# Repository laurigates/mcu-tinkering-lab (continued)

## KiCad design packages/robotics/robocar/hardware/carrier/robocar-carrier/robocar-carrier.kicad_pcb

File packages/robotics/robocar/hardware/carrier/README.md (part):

# robocar carrier PCB

> **Before paying for an order**, Lauri does the bench checks in
> [Pre-order checks still owed](#pre-order-checks-still-owed-lauri);
> [`board.toml`](board.toml) marks every unmeasured dimension (#750).

The **main board**: one 100 × 100 mm, 2-layer PCB, screwed to the chassis (no
ready-made plate; the chassis is drilled to match H1–H4), that replaces the
hand-wired harness in [`WIRING.md`](../../WIRING.md). It carries the motor
driver, the PWM driver, the I2C mux, the GPIO expander and its mirror header,
the amplifier, the 3V3 regulator, the pack's power switch, soft latch and USB-C
charger, the power and peripheral connectors, the buzzer and the test headers.

The XIAO ESP32-S3 Sense rides on a **head board** in the pan-tilt kit's top
cradle. The three head variants are a PCB of their own, the
[head panel](../../head/README.md), ordered apart from this one. A 2 × 8,
2.0 mm-pitch IDC ribbon joins J1 here to the fitted head.

Until #1280 (Lauri, 2026-11-25) the heads were a column on this board's right,
sawn off after delivery; the main board needed their 30 mm for the switch,
latch and charger (ADR-038). The main board is now the whole panel and needs no
sawing. Both KiCad projects come from one [`hardware.toml`](../../hardware.toml):
`board.toml` `[project] side = "main"` here, `side = "head"` there
(`tools/kicad/netlist.py`).

KiCad 10 project: [`robocar-carrier/`](robocar-carrier/). Its
schematic is generated from [`hardware.toml`](../../hardware.toml) and the parts
registry ([`docs/reference/parts/`](../../../../../docs/reference/parts/)) by
`tools/kicad`
([ADR-027](../../../../../docs/decisions/ADR-027-kicad-carrier-generation.md));
the board is placed and routed from the same netlist and
[`board.toml`](board.toml), which holds every position, the bands and the
silkscreen. Never edit the `.kicad_sch` or `.kicad_pcb` in KiCad; change those
files and regenerate (see [Regenerate and check](#regenerate-and-check)).

## What is on it

Each module sits in female headers or plugs into a connector, so any of them can
be swapped without desoldering. The passives and the regulator are SMD on the
top side; everything else is through-hole.

| Ref | Part | Board | Notes |
|---|---|---|---|
| J1 | 2×8 pin header, 2.0 mm, unshrouded | main | The main end of the ribbon, in the front row (pins at x 37.5–51.5). Lauri's 10–15 cm ribbon length was for J1's spot beside the old head column, about 22 mm further right, so check it still reaches. The head end is on the [head panel](../../head/README.md) |
| A1 | SparkFun TB6612FNG, in 2 × 1×8 female headers | main | Motor outputs on its left header |
| A2 | Adafruit PCA9685, in female headers on its JP3 side header and its channel 8–13 PWM pins | main | Motor control lines; servo and LED columns stay on the module |
| A3 | Adafruit TCA9548A, or the wider purple TCA9548A/PCA9548A clone, in female headers | main | Every I2C device sits behind it. The clone's rows are one pitch wider, so the upstream (VIN…SC1) side has a second row of holes one pitch toward the rear, each joined to the hole beside it; see [The TCA9548A socket](#the-tca9548a-socket) |
| A4 | Adafruit MAX98357A, in a 1×7 female header | main | The speaker stays on the module's terminal |
| A5 | CJMCU-2317 (MCP23017), in female headers under all 30 holes | main | On mux channel 2, address 0x20; see [The GPIO expander](#the-gpio-expander) |
| J18 | 2×10 pin header, 2.54 mm | main | The expander's GPIOs, in the module's own order; see [The GPIO expander](#the-gpio-expander) |
| U2 | AMS1117-3.3, SOT-223 | main | The main board's 3V3; the XIAO's 3V3 pad stays open |
| D1 | B5819W Schottky, SOD-123 | main | Between the main board's 5V and the ribbon's 5V conductors (net `XIAO_5V`), beside J1: the XIAO's 5V pad is its USB-C VBUS |
| C1–C3 | 470 µF 16 V electrolytic, 8 × 10.5 mm | main | Bulk on the 5V trunk for the PCA9685 V+ and TB6612FNG VM (C1, C2), and beside the MAX98357A Vin (C3) |
| C4–C6 | 100 nF, 0805 | main | PCA9685 VCC, TCA9548A VIN, MCP23017 VCC (C6, beside the CJMCU-2317's socket) |
| C7, C8 | 22 µF 16 V tantalum, 3528 | main | AMS1117 input and output |
| R1 | 100 Ω, 0805 | main | Buzzer series resistor |
| R2–R11 | 2.2 kΩ, 0805 | main | Pull-ups on mux channels 0–4 (R10, R11 on channel 2); see [Pre-fab review](#pre-fab-review-810) |
| R12, R13 | 2.2 kΩ, 0805 | main | Pull-ups on the upstream I2C bus (the XIAO's SDA and SCL), beside C5 in the row behind A3 |
| F1 | 4 A hold PTC fuse, 16 V, 1812 (BSMD1812-400-16V) | main | After the power switch Q2, ahead of everything else on VBAT, at the rear edge between Q2 and J4; see [The power switch](#the-power-switch) |
| Q1, Q2 | DMP3013SFV P-MOSFET, PowerDI3333-8 (C264098) | main | Back to back: Q1 blocks a reversed pack, Q2 is the switch; see [The power switch](#the-power-switch) |
| R14, R15 | 100 kΩ (C149504), 10 kΩ (C17414), 0805 | main | Q1/Q2 gate pull-up and gate resistor |
| Q3, R16 | 2N7002 (C8545), 10 kΩ 0805 (C17414) | main | The latch's hold FET and its HOLD pull-down |
| D2, D3 | SD101AW Schottky, SOD-123 (C3031887) | main | The latch's button-to-switch and button-to-SENSE diodes; 0.2 µA leakage: a B5819W's would pull the off switch's gate toward its threshold through R14 (`soft-latch` block header) |
| R32 | 10 kΩ, 0805 (C17414) | main | `PWR_SENSE` pull-up to 3V3, so D2's leakage does not read as a held button against the MCP23017's weak pull-up |
| J19 | JST-XH 2-pin | main | Power button lead (a chassis push button, either way round) |
| R17, R18, C9 | 100 kΩ (C149504), 22 kΩ (C17560), 100 nF (C49678), 0805 | main | Pack-voltage divider into D3 and its filter |
| J3 | XT30 (AMASS XT30PW-M) | main | Pack in, at the rear edge on the right, mating face to the rear; pad 1 is "−" |
| U5, L1 | BQ25887RGER (VQFN-24, C2761614), 1 µH 1008 inductor (C435392) | main | The pack's USB charger; see [The USB-C charger](#the-usb-c-charger) |
| C10–C19, R19–R31 | 0805, except C13–C15 (22 µF 25 V X7R, 1210, C309062) | main | The charger block's capacitors and resistors (the block's header lists values and LCSC numbers) |
| F2 | 2 A hold PTC fuse, 16 V, 1812 (C883156) | main | The charger's BAT branch, between U5's BAT capacitors and J3's "+" (`CHG_BAT` to `PACK_IN`) |
| C20 | 100 µF 16 V electrolytic, 6.3 × 5.8 mm (Panasonic EEE-FK1C101P, C128532) | main | Damps the pack lead's ring against the BAT branch's ceramics at plug-in; see [The USB-C charger](#the-usb-c-charger) |
| D4, R33 | Red LED 0805 (NCD0805R1, C84256), 1.5 kΩ 0805 (C4310) | main | Charge status on U5's STAT: on while charging, off when done, blinking at 1 Hz on a fault |
| J20 | USB-C receptacle, USB 2.0 16-pin (HRO TYPE-C-31-M-12, C165948) | main | Charge-only port at the right edge; not the XIAO's USB-C, and not connected to its 5V pin |
| J21 | JST-XH 3-pin | main | Pack balance lead: only pin 2, the cells' midpoint, is wired |
| J4 | JST VH 4-pin (B4P-VH), 3.96 mm | main | LM2596 module: IN+, IN−, OUT+, OUT−, at the rear edge turned 180° so IN+ is its right-hand pin, nearest F1; the silkscreen prints "O- O+ I- I+" above the pins, left to right, and "SET LM2596 TO 5.0V FIRST" beside it |
| J5, J6 | JST-XH 2-pin | main | Left and right motor, side by side at A1's motor outputs |
| J7, J8 | JST-XH 4-pin | main | RCWL-1601 front and rear, I2C mode: VCC, SCL, SDA, GND (silkscreen "V C D G"); side by side at the front edge |
| J9 | JST-XH 4-pin | main | SSD1306 0.91" OLED: GND, VCC, SCL, SDA (silkscreen "G V C D") |
| BZ1 | 12 mm buzzer, 7.6 mm pin pitch | main | Soldered to the board; + on pad 1, beside the silkscreen "+" |
| J11–J15 | 1×4 and 1×2 pin headers | main | Test headers, see [Debug headers](#debug-headers) |
| H1–H4 | M3 holes | main | Chassis (drilled to match), at the four corners; H2 and H4 moved from x 65 to x 96 with #1280 |

The per-part values, LCSC numbers and the reasons for each are in
[`hardware.toml`](../../hardware.toml); the pin orders are in the registry entries
it names.

## The three heads

The heads are the [head panel](../../head/README.md#the-three-heads)'s three
variants: where each one puts the ribbon header, and the cradle's M2 holes.
Moving the ribbon to another head moves the robot to it; the main board has a
single end, J1.

## The ribbon survives a reversed plug

The headers are unshrouded 2.0 mm-pitch pin headers, mated by a 2.0 mm IDC plug
on 1.0 mm-pitch flat ribbon. The plug fits either way round, which takes
pin *n* to pin 17 − *n*. The pinout in
[`idc-2x08-xiao-cable.toml`](../../../../../docs/reference/parts/idc-2x08-xiao-cable.toml)
pairs each pin with one it can safely swap with: 5 V lands on 5 V, GND on GND,
SDA on SCL, the pack divider's D3 (the one XIAO input) on the unconnected
pin 9, and every other XIAO output on another main-board input. UART0 TX lands
on the latch's HOLD and idles high, so a reversed plug latches the robot on and
firmware cannot switch it off: unplug the pack. The ribbon grew from 14 to 16 ways for the power
latch's HOLD and the divider (ADR-038, #1270), because the carrier's only spare
XIAO pads, D3 and D7, are on the head and the switch is on the main board. **A reversed plug damages nothing and does not work, and the robot stays on until the pack is unplugged.**
If the robot is dead after reassembly, check the plug orientation first: every
header prints a pin-1 mark.

## The power switch

ADR-038 / #1270. The pack input is the circuit block
[`pack-input-pfet-switched`](../../../../../docs/reference/blocks/pack-input-pfet-switched.toml)
driven by [`soft-latch`](../../../../../docs/reference/blocks/soft-latch.toml)
(both first uses on a board), plus a pack-voltage divider. J3 pin 2 (+) goes to
Q1, then Q2 and F1 to VBAT.

- **Switch.** Q1 and Q2 are DMP3013SFV, back to back, gates tied (`PACK_GATE`).
  The switch carries about 76 µA of gate current and nothing when off. 2S
  ratings against this pack: 30 V and ±25 V VGSS against 8.4 V full and a 16.8 V
  hot-plug ring; F1 is 16 V. VGS = −0.91 × the pack, so −5.6 V at 6.2 V, inside
  the −4.5 V RDS(on) row (DS40141 Rev. 5-2). Channel loss at the 3.4 A stall
  current is about 0.2 W per FET (estimate). The block has no gate clamp, so it
  is 2S only; the balancebot's 3S/4S version is #1273.
- **F1** is the 4 A hold part of #810 (the block's own is 3 A), now after the
  FETs. The 23 mm of `PACK_IN` from J3 to Q1's drain has no fuse ahead of it;
  the pack's BMS covers a short there. The charger's branch off `PACK_IN` has
  its own fuse, F2.
- **Latch.** One button (J19, a chassis push button on a JST-XH lead) closes
  `PWR_BTN` to GND, which turns the pack on. The XIAO boots with the button still
  held, and firmware drives HOLD (D7, GPIO44) high as early as it can; the 10 kΩ
  pull-down R16 keeps it low while the MCU is unpowered, against GPIO44's
  internal pull-up at reset. Driving HOLD low
  switches the robot off once the button is released. A firmware hang with HOLD
  high cannot be undone by the button: unplug the pack. Not measured: how long
  the button has to be held at boot.
- **Button on a lead, not on the board.** The repo's tact switch entry has no
  LCSC number until its JLCPCB rotation is checked by hand, and a chassis button
  is where a person reaches. `PWR_BTN` sits at the pack voltage less one Schottky
  drop while the robot is off (about 76 µA behind it), so the lead has no TVS;
  the `button-input` block's 5 V TVS and 3V3 pull-up cannot be used there.
- **SENSE** (button read-back, for a long-press switch-off) goes to the
  MCP23017's GPB0 (net `PWR_SENSE`, also on J18 pin 6) because no XIAO pad is
  left. A robot without the expander fitted cannot be switched off from the
  button, and the button cannot wake it from deep sleep; the pack-voltage cutoff
  does not need it.
- **Divider.** R17 (100 kΩ, from VBAT after the switch) over R18 (22 kΩ), C9
  100 nF at the ribbon's J1 end, into D3 (GPIO4, ADC1_CH3) via ribbon pin 8: 8.4 V reads
  1.51 V, 6.0 V reads 1.08 V, 69 µA at 8.4 V. The source impedance is 18 kΩ, so
  C9 supplies the sampling charge. The ratio is balancebot's rev3 ratio.

Final nets and pins for the firmware (#1271): `PWR_HOLD` is `POWER_HOLD_PIN`,
GPIO44 (D7, ribbon pin 11); `PACK_SENSE` is `PACK_SENSE_PIN`, GPIO4 (D3, ribbon
pin 8); `PWR_SENSE` is `POWER_BUTTON_EXPANDER_PIN`, MCP23017 GPB0 (pin 8).

**Layout** (#1280). The pack path runs along the rear edge, right to left, all
on F.Cu with no via: J3's "+" to Q1's drain on a fixed 2 mm track, Q1 and Q2
facing each other (common source tied pin to pin, joined across by a 1.0 mm
segment between the two gate pads), Q2's drain into F1 at 2 mm, and F1 into
J4's IN+ at 2 mm. R14 and R15 sit north of the FETs; the gates sit at
opposite corners of the pair, so PACK_GATE reaches Q1's through B.Cu. The latch
(D2, D3, Q3, R16) and the button lead J19 are above J3; the divider (R17, R18,
C9) is at the front, by J1 and J15. `board.toml` gives the reasons for each
fixed track.

## The USB-C charger

ADR-038 / #1272. The circuit block
[`bq25887-2s-usb-charger`](../../../../../docs/reference/blocks/bq25887-2s-usb-charger.toml)
(first use on a board) charges the 2S pack from a 5 V USB-C port on J20 and
balances the cells. The block's header holds the datasheet reasoning, the IC
comparison against the MP2672A, and every number below.

- **The port reaches nothing but the charger.** `CHG_VBUS` joins J20's four
  VBUS pins, U5's VBUS pin and C10, and no rail names it besides. The XIAO's 5V
  pad is its own VBUS (#1252), so the netlist test
  (`RobocarChargerTests`) pins `CHG_VBUS` to those pins. J20's CC1 and CC2 each
  have a 5.1 kΩ pull-down (R30, R31): a sink that asks for 5 V and negotiates
  nothing. D+, D− and SBU are open. J20's shield and GND pins go to GND.
- **BAT reaches `PACK_IN` through F2**, on the pack side of Q1, so the pack
  charges with the robot off, through J3 pin 2 and the pack's BMS. The charge
  current does not go through F1 or the switch FETs.
- **Plug-in ring.** With Q1 and Q2 off, about 86 µF of ceramic sits on
  `CHG_BAT` (C16, C17, and C13–C15 through the charger's sense path). Against
  the pack lead's inductance (about 0.3 µH, assumed) it rings at plug-in, to an
  estimated 10–11 V against BAT's and SNS's 12 V absolute maximum (SLUSD89B
  §7.1). C20, a 100 µF electrolytic (0.36 Ω at 100 kHz), adds lossy
  capacitance across the ceramics; F2 in series does much of the damping. The
  third review round's simulation puts the peak at 9.7–10.6 V with C20 against
  11.1–13.0 V without, and 10.3–11.6 V with C20 cold. Simulated, not measured:
  scope `PACK_IN` at XT30 insertion on the first board (#1307).
- **Charge-status LED.** D4 lights from REGN through R33 (1.5 kΩ) into STAT,
  which is open drain: on while charging, off when the charge ends or is
  disabled, blinking at 1 Hz on any fault (SLUSD89B §6). About 1.9 mA, and
  2.4 mA at most against STAT's 6 mA sink rating (§7.1). REGN is up only while
  the port has power, so D4 is dark with no USB plugged in.
- **Input and charge current.** R19 (820 Ω) caps the input at 1.35 A typical,
  1.56 A at the part's maximum (datasheet constant KILIM). That gives about
  0.83 A into the pack (0.96 A at the maximum), where ADR-038's estimate was
  1 A from 2 A of input. For 2 × 18650 of 2500–3500 mAh that is 3–4.5 hours
  (estimate, not measured).
- **No power path.** With the robot on, the robot's load comes out of the
  charge current first, and the charger cannot see the current fall at the end
  of the cycle, so it holds 4.20 V per cell until its 12 hour timer ends it.
  Charge with the robot off.
- **Balancing.** R21–R24 (4 × 200 Ω in parallel) set about 82 mA, from the
  part's own defaults, with no host. The cells' midpoint comes in on J21 pin 2.
  **J21 pins 1 and 3 are the raw cell terminals and stay unwired**: a wire from
  either to GND or `PACK_IN` would bypass the pack's BMS switch. The pack's BMS
  stays, and both circuits only discharge the higher cell, so they do not
  fight. The BMS's over-charge cutoff must sit above 4.221 V per cell or it
  cuts an ordinary charge; this pack's BMS is not recorded in the repo.
- **Plug J21 in before charging.** With J21 unplugged, MID floats, and
  SLUSD89B does not say what the charger does with MID open, so a charge could
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
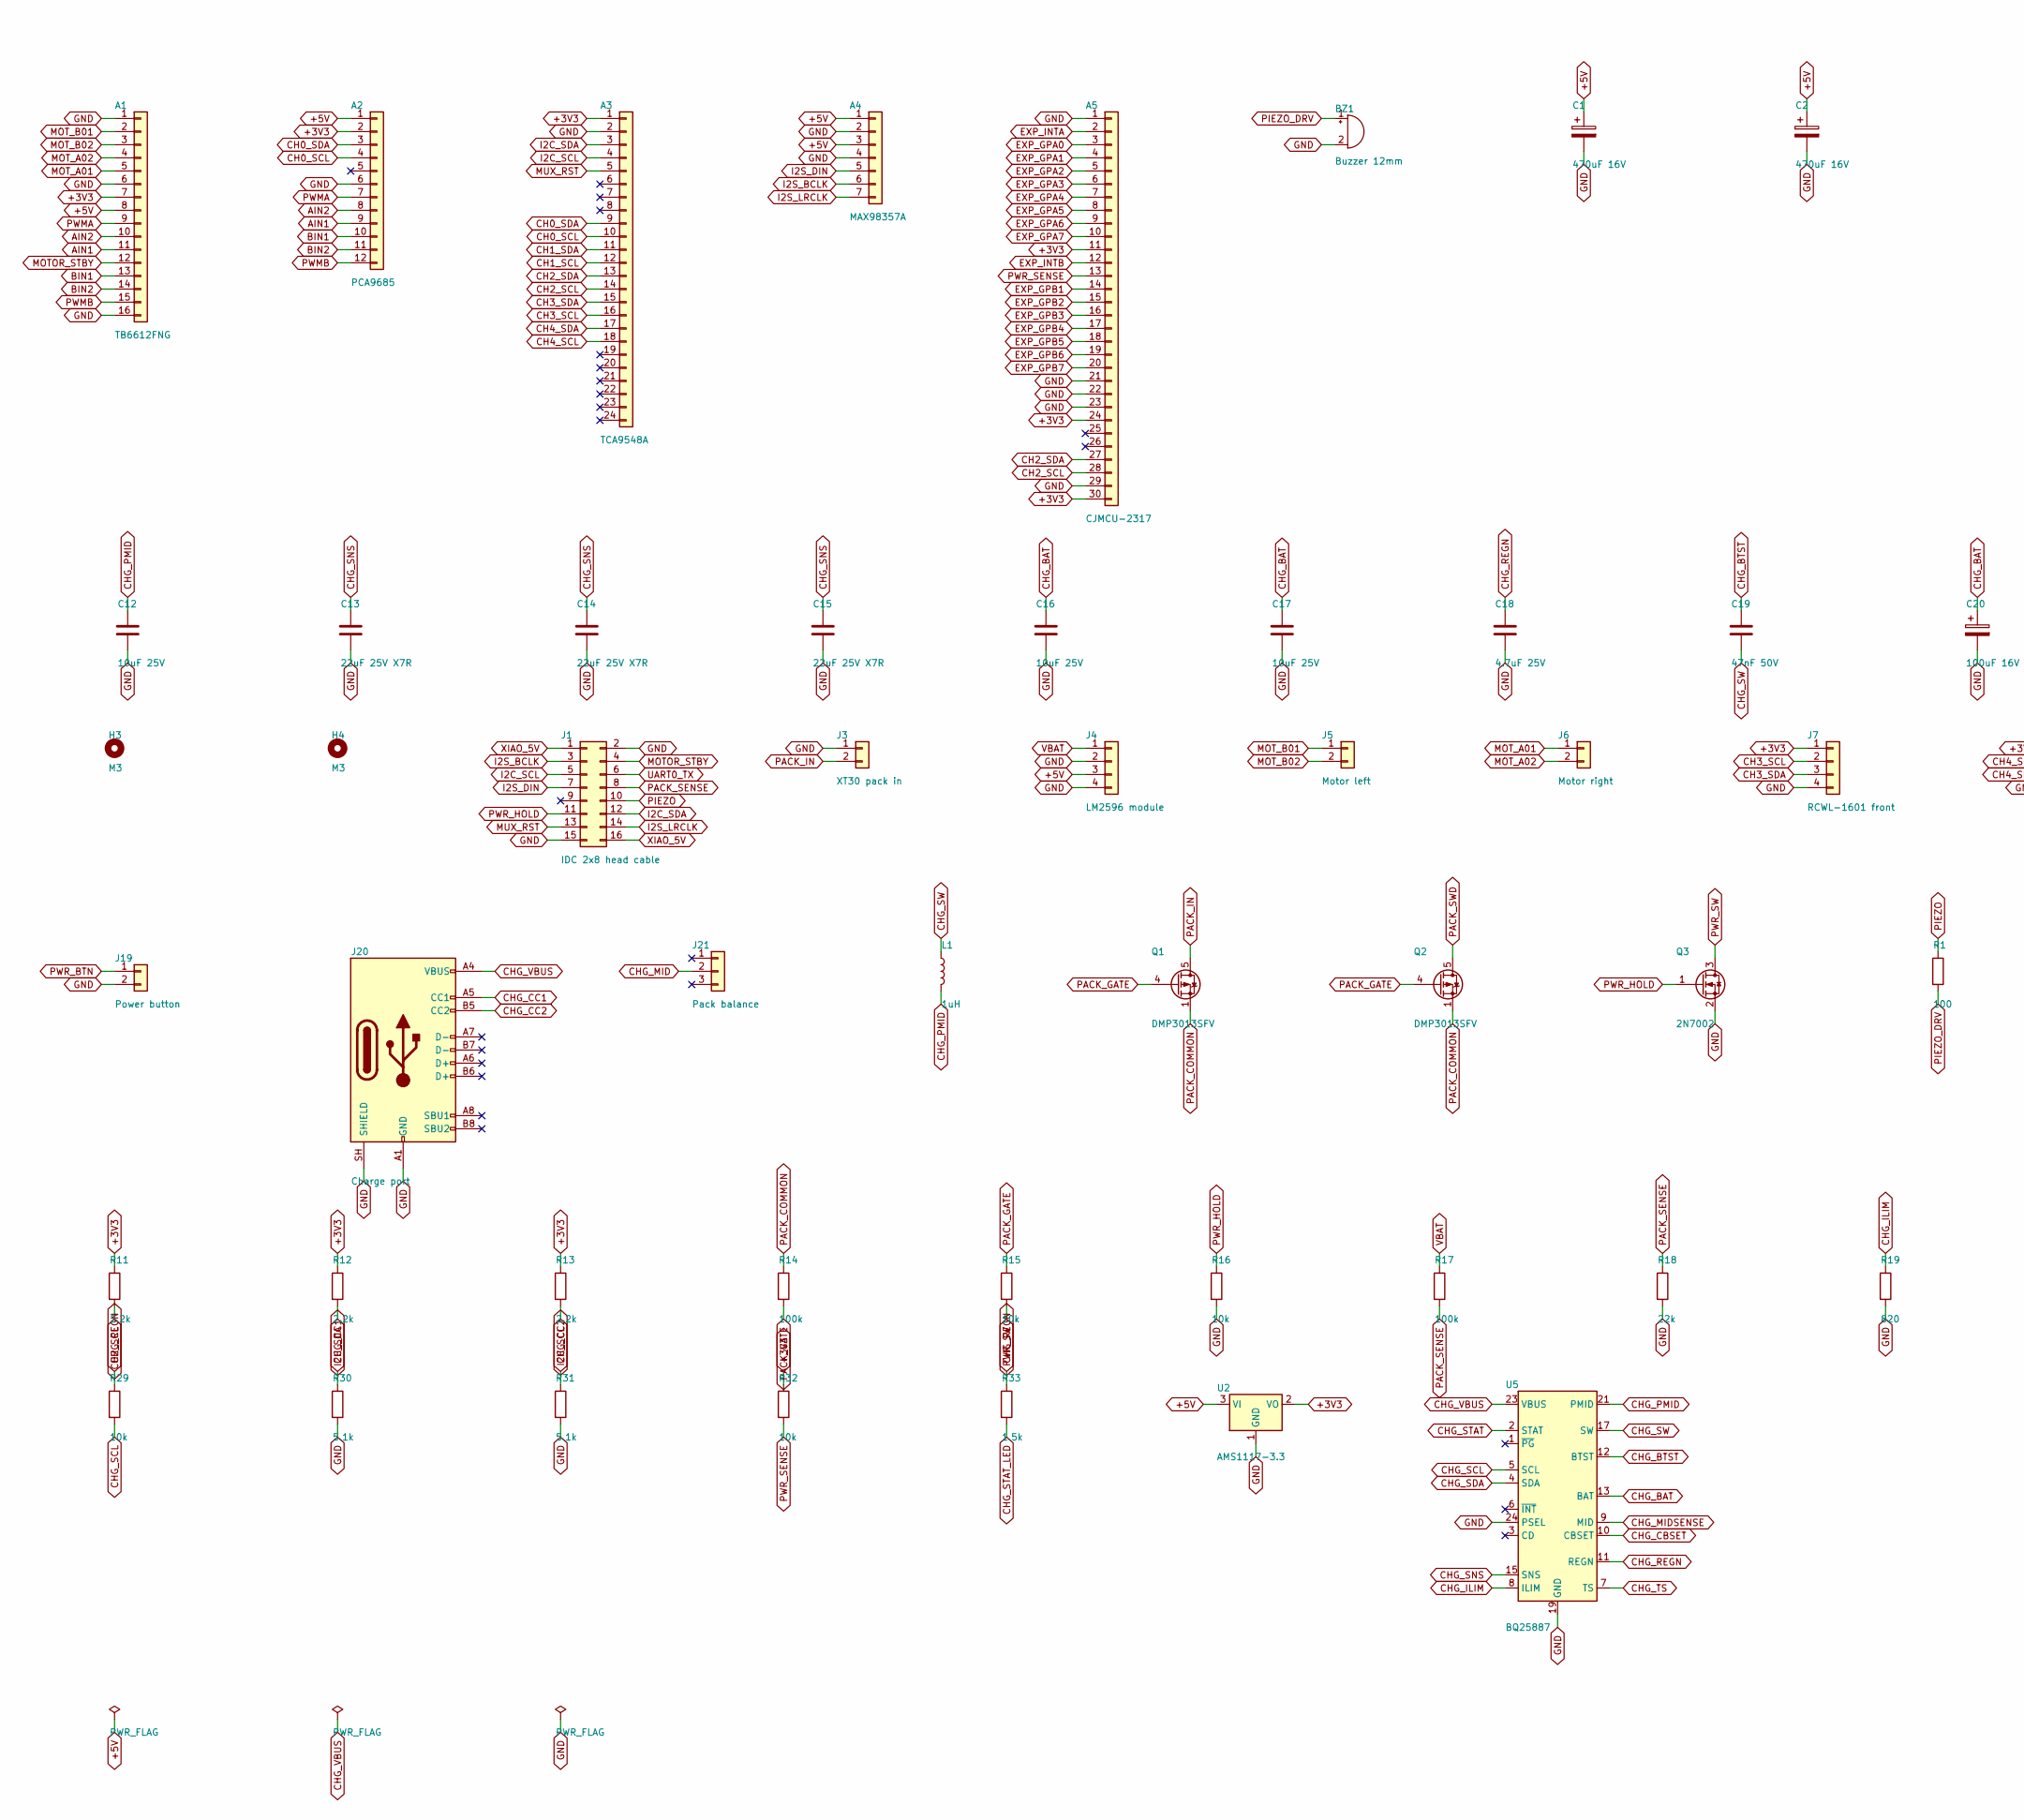
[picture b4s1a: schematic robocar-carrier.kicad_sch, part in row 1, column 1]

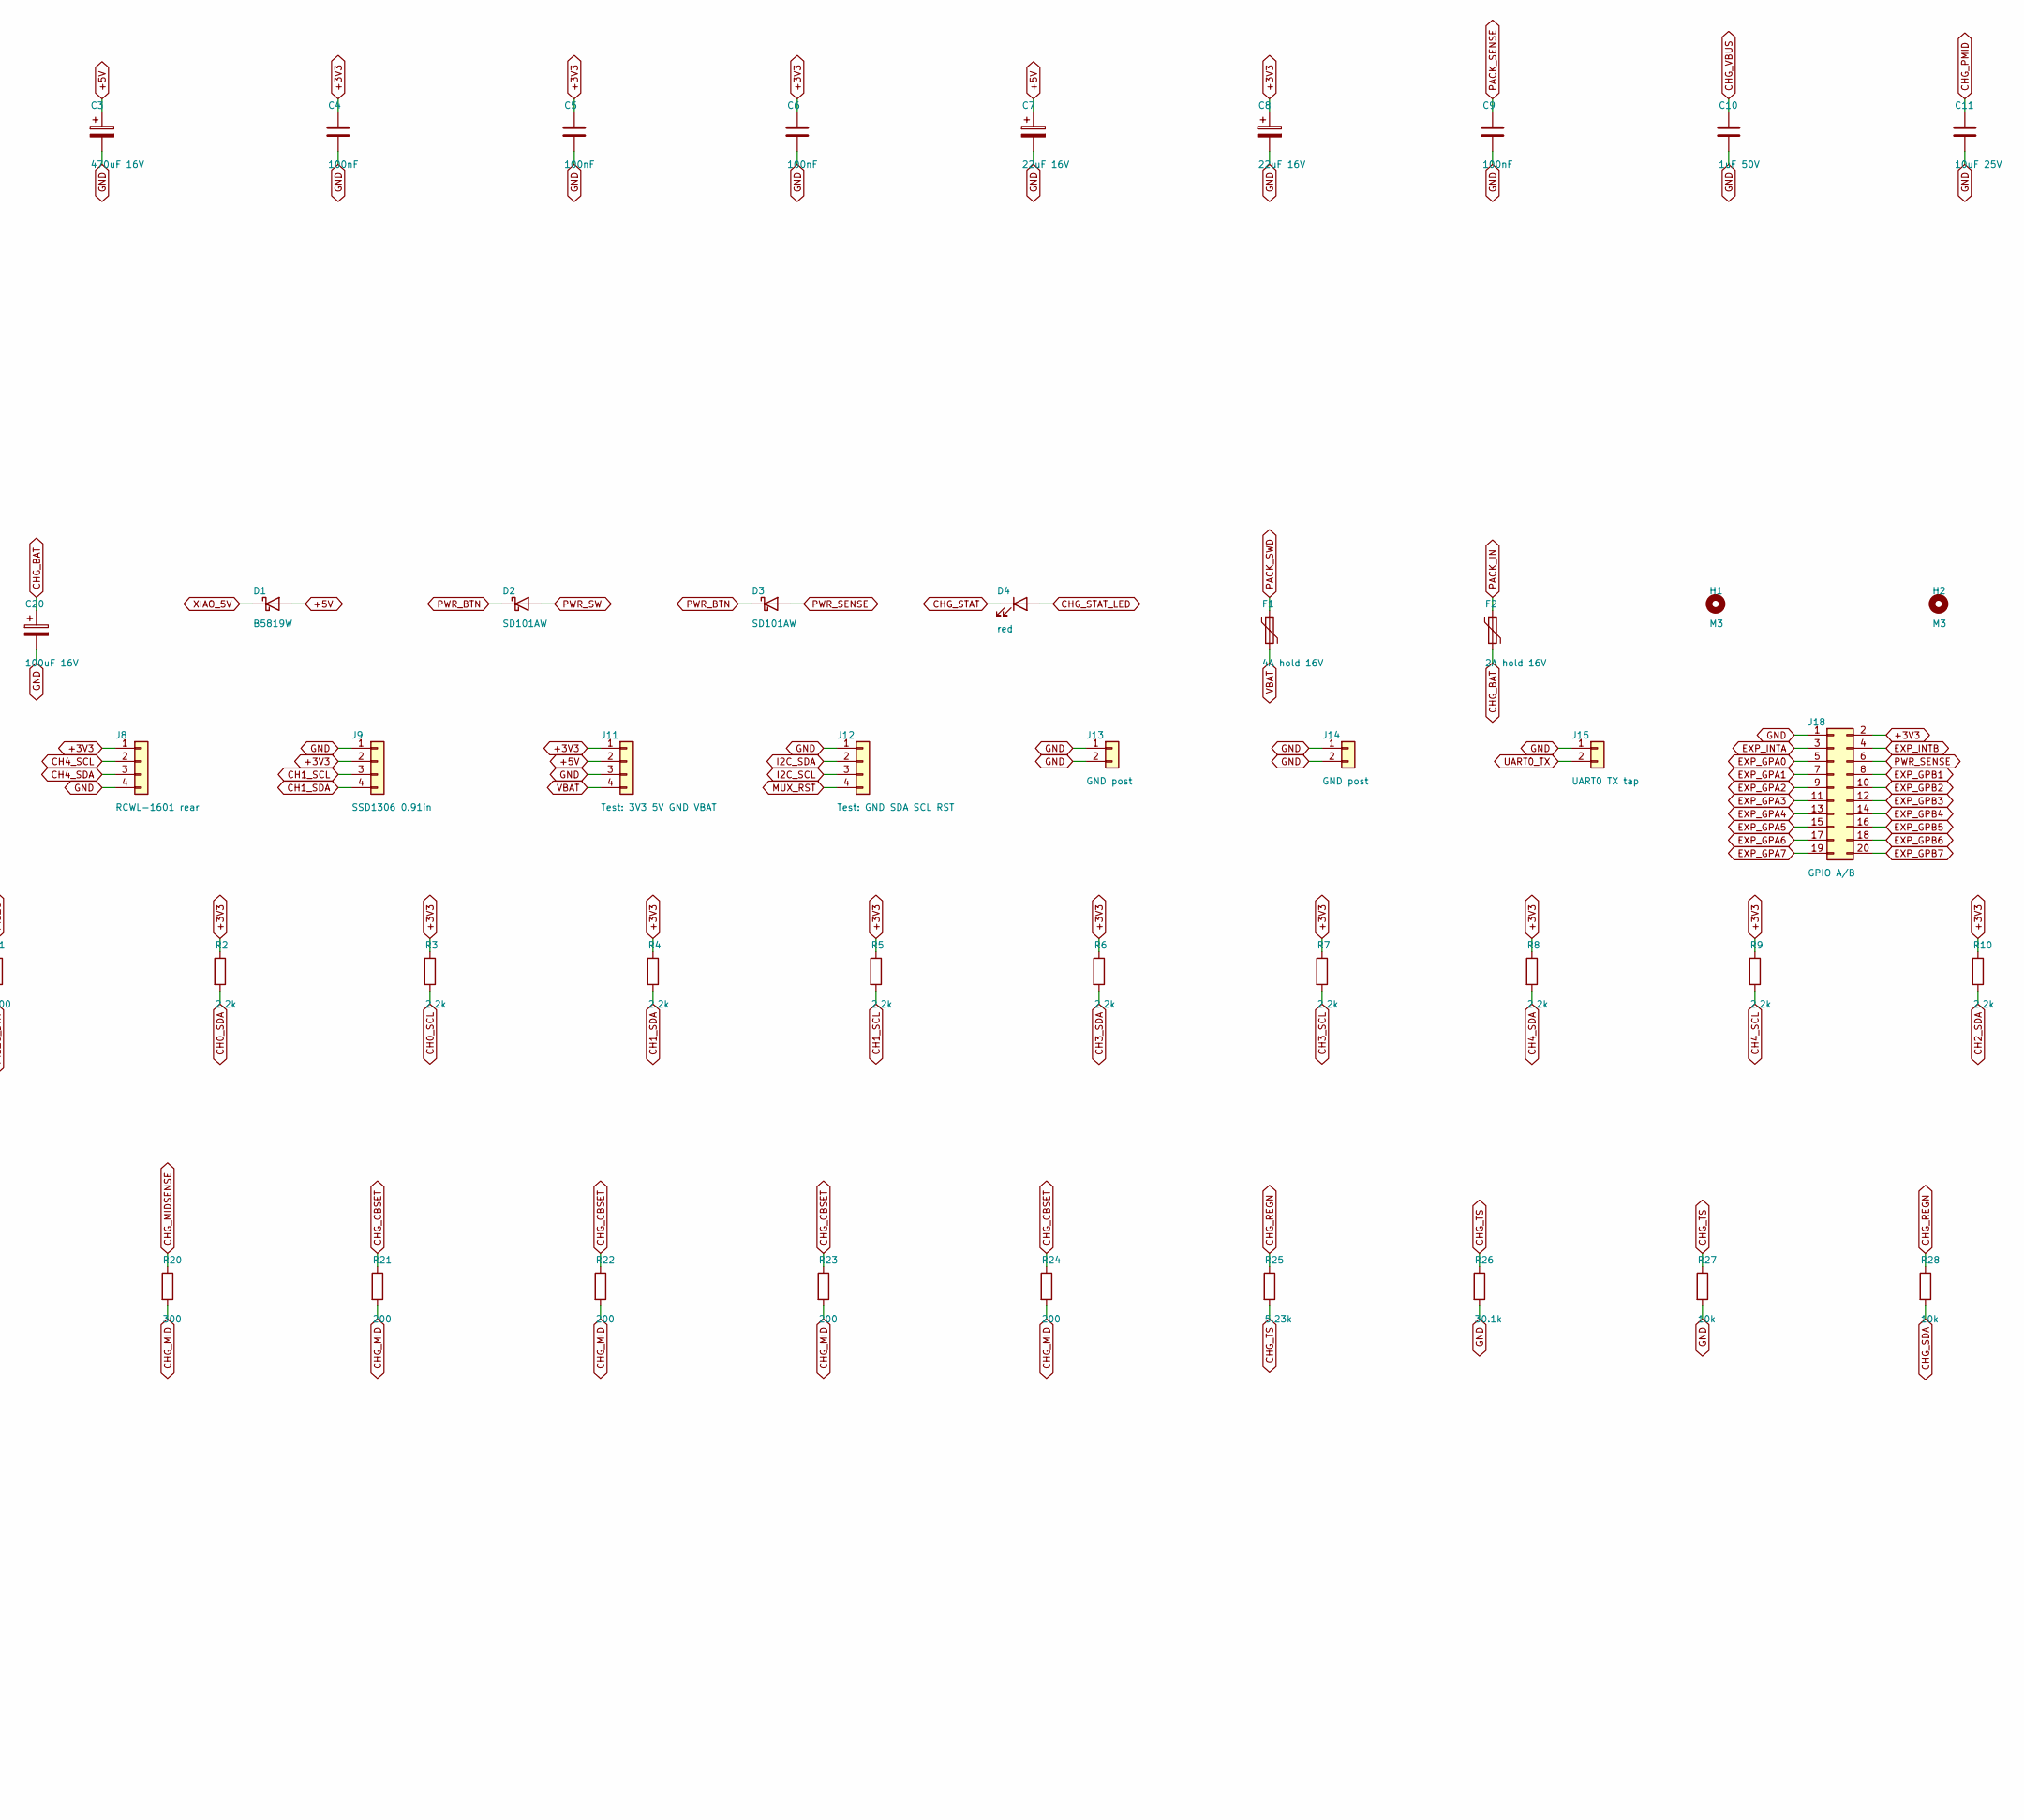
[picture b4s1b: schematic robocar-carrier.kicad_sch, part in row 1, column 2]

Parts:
A1: TB6612FNG; SparkFun_TB6612FNG_Socket
A2: PCA9685; Adafruit_PCA9685_Socket
A3: TCA9548A; Adafruit_TCA9548A_Socket
A4: MAX98357A; Adafruit_MAX98357A_Socket
A5: CJMCU-2317; CJMCU_2317_Socket
BZ1: Buzzer 12mm; Buzzer_12x9.5RM7.6
C1, C2, C3: 470uF 16V; CP_Elec_8x10.5; LCSC C96179
C4, C5, C6, C9: 100nF; C_0805_2012Metric_Pad1.18x1.45mm_HandSolder; LCSC C49678
C7, C8: 22uF 16V; CP_EIA-3528-21_Kemet-B_HandSolder; LCSC C8020
C10: 1uF 50V; C_0805_2012Metric_Pad1.18x1.45mm_HandSolder; LCSC C28323
C11, C12, C16, C17: 10uF 25V; C_0805_2012Metric_Pad1.18x1.45mm_HandSolder; LCSC C15850
C13, C14, C15: 22uF 25V X7R; C_1210_3225Metric_Pad1.33x2.70mm_HandSolder; LCSC C309062
C18: 4.7uF 25V; C_0805_2012Metric_Pad1.18x1.45mm_HandSolder; LCSC C1779
C19: 47nF 50V; C_0805_2012Metric_Pad1.18x1.45mm_HandSolder; LCSC C107154
C20: 100uF 16V; CP_Elec_6.3x5.8; LCSC C128532
D1: B5819W; D_SOD-123; LCSC C8598
D2, D3: SD101AW; D_SOD-123; LCSC C3031887
D4: red; LED_0805_2012Metric_Pad1.15x1.40mm_HandSolder; LCSC C84256
F1: 4A hold 16V; Fuse_1812_4532Metric_Pad1.30x3.40mm_HandSolder; LCSC C47263807
F2: 2A hold 16V; Fuse_1812_4532Metric_Pad1.30x3.40mm_HandSolder; LCSC C883156
H1, H2, H3, H4: M3; MountingHole_3.2mm_M3
J1: IDC 2x8 head cable; PinHeader_2x08_P2.00mm_Vertical
J3: XT30 pack in; AMASS_XT30PW-M_1x02_P2.50mm_Horizontal
J4: LM2596 module; JST_VH_B4P-VH_1x04_P3.96mm_Vertical
J5: Motor left; JST_XH_B2B-XH-A_1x02_P2.50mm_Vertical
J6: Motor right; JST_XH_B2B-XH-A_1x02_P2.50mm_Vertical
J7: RCWL-1601 front; JST_XH_B4B-XH-A_1x04_P2.50mm_Vertical
J8: RCWL-1601 rear; JST_XH_B4B-XH-A_1x04_P2.50mm_Vertical
J9: SSD1306 0.91in; JST_XH_B4B-XH-A_1x04_P2.50mm_Vertical
J11: Test: 3V3 5V GND VBAT; PinHeader_1x04_P2.54mm_Vertical
J12: Test: GND SDA SCL RST; PinHeader_1x04_P2.54mm_Vertical
J13, J14: GND post; PinHeader_1x02_P2.54mm_Vertical
J15: UART0 TX tap; PinHeader_1x02_P2.54mm_Vertical
J18: GPIO A/B; PinHeader_2x10_P2.54mm_Vertical
J19: Power button; JST_XH_B2B-XH-A_1x02_P2.50mm_Vertical
J20: Charge port; USB_C_Receptacle_HRO_TYPE-C-31-M-12; LCSC C165948
J21: Pack balance; JST_XH_B3B-XH-A_1x03_P2.50mm_Vertical
L1: 1uH; L_1008_2520Metric; LCSC C435392
Q1, Q2: DMP3013SFV; Diodes_PowerDI3333-8; LCSC C264098
Q3: 2N7002; SOT-23; LCSC C8545
R1: 100; R_0805_2012Metric_Pad1.20x1.40mm_HandSolder; LCSC C17408
R2, R3, R4, R5, R6, R7, R8, R9, R10, R11, R12, R13: 2.2k; R_0805_2012Metric_Pad1.20x1.40mm_HandSolder; LCSC C17520
R14, R17: 100k; R_0805_2012Metric_Pad1.20x1.40mm_HandSolder; LCSC C149504
R15, R16, R27, R28, R29, R32: 10k; R_0805_2012Metric_Pad1.20x1.40mm_HandSolder; LCSC C17414
R18: 22k; R_0805_2012Metric_Pad1.20x1.40mm_HandSolder; LCSC C17560
R19: 820; R_0805_2012Metric_Pad1.20x1.40mm_HandSolder; LCSC C17837
R20: 300; R_0805_2012Metric_Pad1.20x1.40mm_HandSolder; LCSC C17617
R21, R22, R23, R24: 200; R_0805_2012Metric_Pad1.20x1.40mm_HandSolder; LCSC C17540
R25: 5.23k; R_0805_2012Metric_Pad1.20x1.40mm_HandSolder; LCSC C17739
R26: 30.1k; R_0805_2012Metric_Pad1.20x1.40mm_HandSolder; LCSC C21841
R30, R31: 5.1k; R_0805_2012Metric_Pad1.20x1.40mm_HandSolder; LCSC C27834
R33: 1.5k; R_0805_2012Metric_Pad1.20x1.40mm_HandSolder; LCSC C4310
U2: AMS1117-3.3; SOT-223-3_TabPin2; LCSC C6186
U5: BQ25887; Texas_RGE0024H_VQFN-24-1EP_4x4mm_P0.5mm_EP2.7x2.7mm; LCSC C2761614

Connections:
+3V3: A1.7, A2.2, A3.1, A5.11, A5.24, A5.30, C4.1, C5.1, C6.1, C8.1, J7.1, J8.1, J9.2, J11.1, J18.2, R2.1, R3.1, R4.1, R5.1, R6.1, R7.1, R8.1, R9.1, R10.1, R11.1, R12.1, R13.1, R32.1, U2.2 (VO)
+5V: A1.8, A2.1, A4.1, A4.3, C1.1, C2.1, C3.1, C7.1, D1.2 (A), J4.3, J11.2, U2.3 (VI)
AIN1: A1.11, A2.9
AIN2: A1.10, A2.8
BIN1: A1.13, A2.10
BIN2: A1.14, A2.11
CH0_SCL: A2.4, A3.10, R3.2
CH0_SDA: A2.3, A3.9, R2.2
CH1_SCL: A3.12, J9.3, R5.2
CH1_SDA: A3.11, J9.4, R4.2
CH2_SCL: A3.14, A5.28, R11.2
CH2_SDA: A3.13, A5.27, R10.2
CH3_SCL: A3.16, J7.2, R7.2
CH3_SDA: A3.15, J7.3, R6.2
CH4_SCL: A3.18, J8.2, R9.2
CH4_SDA: A3.17, J8.3, R8.2
CHG_BAT: C16.1, C17.1, C20.1, F2.2, U5.13 (BAT), U5.14 (BAT)
CHG_BTST: C19.1, U5.12 (BTST)
CHG_CBSET: R21.1, R22.1, R23.1, R24.1, U5.10 (CBSET)
CHG_CC1: J20.A5 (CC1), R30.1
CHG_CC2: J20.B5 (CC2), R31.1
CHG_ILIM: R19.1, U5.8 (ILIM)
CHG_MID: J21.2, R20.2, R21.2, R22.2, R23.2, R24.2
CHG_MIDSENSE: R20.1, U5.9 (MID)
CHG_PMID: C11.1, C12.1, L1.2, U5.21 (PMID), U5.22 (PMID)
CHG_REGN: C18.1, R25.1, R28.1, R29.1, R33.1, U5.11 (REGN)
CHG_SCL: R29.2, U5.5 (SCL)
CHG_SDA: R28.2, U5.4 (SDA)
CHG_SNS: C13.1, C14.1, C15.1, U5.15 (SNS), U5.16 (SNS)
CHG_STAT: D4.1 (K), U5.2 (STAT)
CHG_STAT_LED: D4.2 (A), R33.2
CHG_SW: C19.2, L1.1, U5.17 (SW), U5.18 (SW)
CHG_TS: R25.2, R26.1, R27.1, U5.7 (TS)
CHG_VBUS: C10.1, J20.A4 (VBUS), J20.A9 (VBUS), J20.B4 (VBUS), J20.B9 (VBUS), U5.23 (VBUS)
EXP_GPA0: A5.3, J18.5
EXP_GPA1: A5.4, J18.7
EXP_GPA2: A5.5, J18.9
EXP_GPA3: A5.6, J18.11
EXP_GPA4: A5.7, J18.13
EXP_GPA5: A5.8, J18.15
EXP_GPA6: A5.9, J18.17
EXP_GPA7: A5.10, J18.19
EXP_GPB1: A5.14, J18.8
EXP_GPB2: A5.15, J18.10
EXP_GPB3: A5.16, J18.12
EXP_GPB4: A5.17, J18.14
EXP_GPB5: A5.18, J18.16
EXP_GPB6: A5.19, J18.18
EXP_GPB7: A5.20, J18.20
EXP_INTA: A5.2, J18.3
EXP_INTB: A5.12, J18.4
GND: A1.1, A1.6, A1.16, A2.6, A3.2, A4.2, A4.4, A5.1, A5.21, A5.22, A5.23, A5.29, BZ1.2 (-), C1.2, C2.2, C3.2, C4.2, C5.2, C6.2, C7.2, C8.2, C9.2, C10.2, C11.2, C12.2, C13.2, C14.2, C15.2, C16.2, C17.2, C18.2, C20.2, J1.2, J1.15, J3.1, J4.2, J4.4, J7.4, J8.4, J9.1, J11.3, J12.1, J13.1, J13.2, J14.1, J14.2, J15.1, J18.1, J19.2, J20.A1 (GND), J20.A12 (GND), J20.B1 (GND), J20.B12 (GND), J20.SH (SHIELD), Q3.2 (S), R16.2, R18.2, R19.2, R26.2, R27.2, R30.2, R31.2, U2.1 (GND), U5.19 (GND), U5.20 (GND), U5.24 (PSEL), U5.25 (GND)
I2C_SCL: A3.4, J1.5, J12.3, R13.2
I2C_SDA: A3.3, J1.12, J12.2, R12.2
I2S_BCLK: A4.6, J1.3
I2S_DIN: A4.5, J1.7
I2S_LRCLK: A4.7, J1.14
MOTOR_STBY: A1.12, J1.4
MOT_A01: A1.5, J6.1
MOT_A02: A1.4, J6.2
MOT_B01: A1.2, J5.1
MOT_B02: A1.3, J5.2
MUX_RST: A3.5, J1.13, J12.4
PACK_COMMON: Q1.1 (S), Q1.2 (S), Q1.3 (S), Q2.1 (S), Q2.2 (S), Q2.3 (S), R14.1
PACK_GATE: Q1.4 (G), Q2.4 (G), R14.2, R15.1
PACK_IN: F2.1, J3.2, Q1.5 (D)
PACK_SENSE: C9.1, J1.8, R17.2, R18.1
PACK_SWD: F1.1, Q2.5 (D)
PIEZO: J1.10, R1.1
PIEZO_DRV: BZ1.1 (+), R1.2
PWMA: A1.9, A2.7
PWMB: A1.15, A2.12
PWR_BTN: D2.1 (K), D3.1 (K), J19.1
PWR_HOLD: J1.11, Q3.1 (G), R16.1
PWR_SENSE: A5.13, D3.2 (A), J18.6, R32.2
PWR_SW: D2.2 (A), Q3.3 (D), R15.2
UART0_TX: J1.6, J15.2
VBAT: F1.2, J4.1, J11.4, R17.1
XIAO_5V: D1.1 (K), J1.1, J1.16

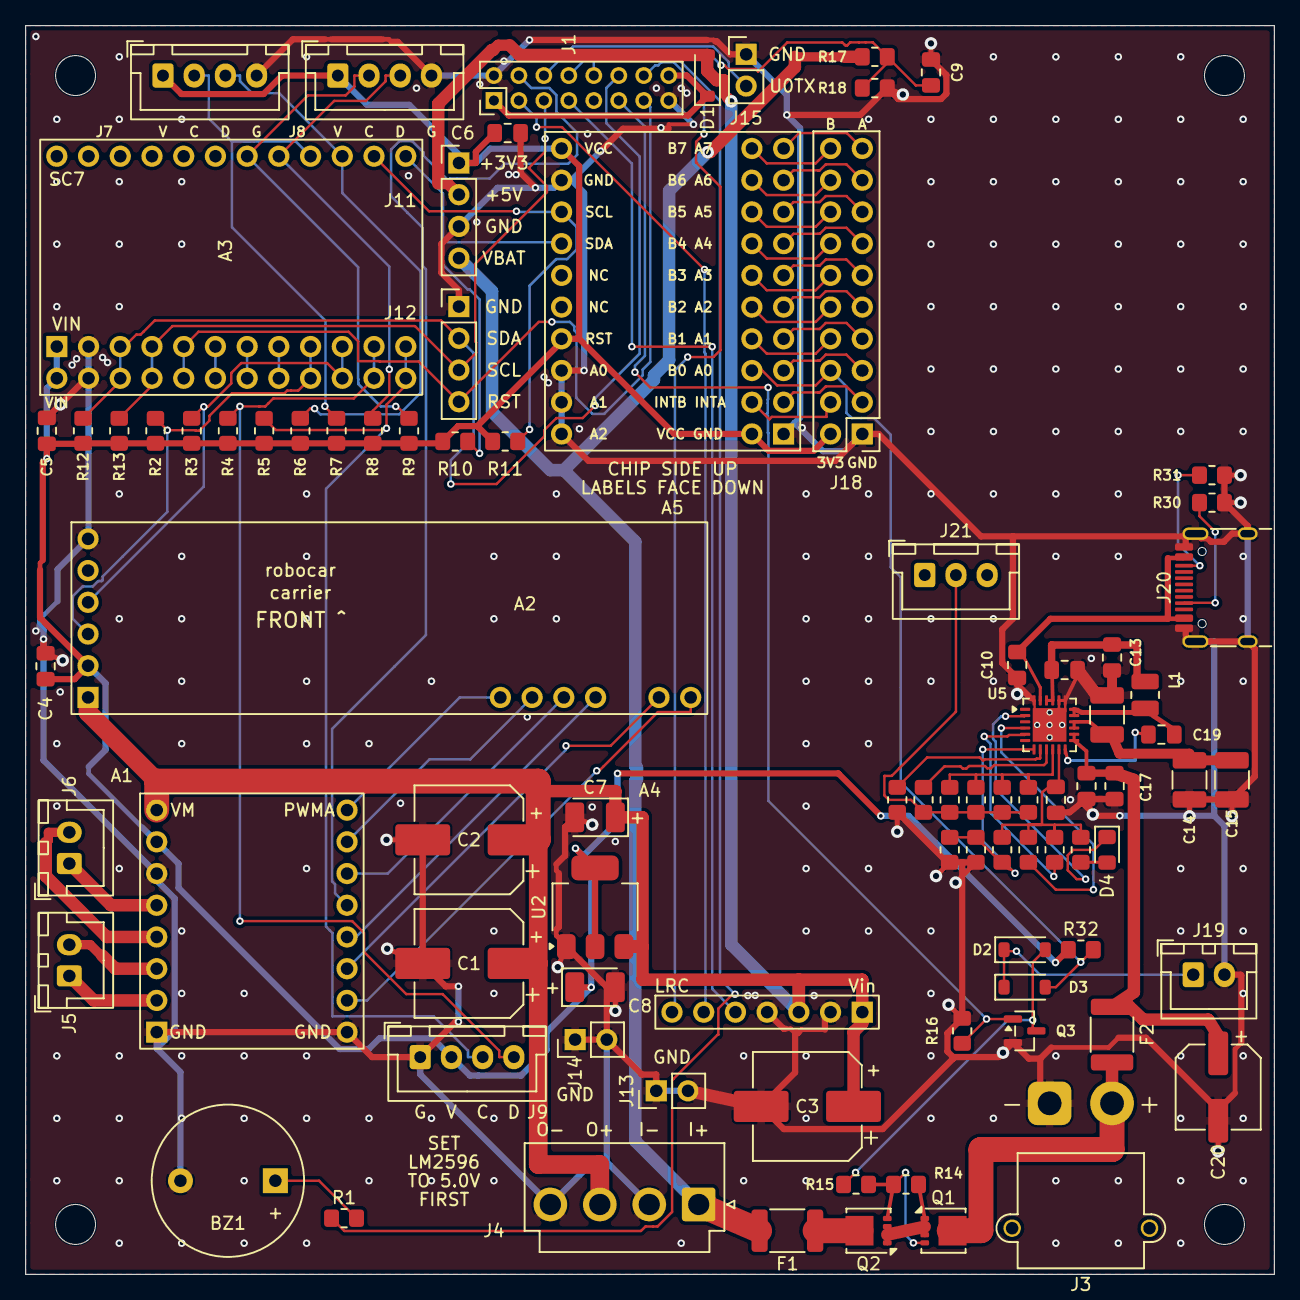
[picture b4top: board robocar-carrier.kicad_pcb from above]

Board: 2 copper layers, 100.0 x 100.0 mm, 92 parts (0 on the bottom side), 79 nets.

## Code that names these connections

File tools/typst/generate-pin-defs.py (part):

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# fmt: off
ROBOCAR_EXTRACT = [
    # ── I2C Bus ──
    ("I2C Bus", "I2C_SDA_PIN",        "I2C_SDA_PIN",        None),
    ("I2C Bus", "I2C_SCL_PIN",        "I2C_SCL_PIN",        None),
    ("I2C Bus", "I2C_MASTER_FREQ_HZ", "I2C_FREQ_HZ",        None),

    # ── TCA9548A Multiplexer ──
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    ("TCA9548A Multiplexer", "I2C_BUS_CHANNEL_MCP23017",  "TCA_CH_MCP23017", None),
    ("TCA9548A Multiplexer", "I2C_BUS_CHANNEL_RANGER_FRONT", "TCA_CH_RANGER_FRONT", None),
    ("TCA9548A Multiplexer", "I2C_BUS_CHANNEL_RANGER_REAR",  "TCA_CH_RANGER_REAR",  None),
    ("TCA9548A Multiplexer", "TCA9548A_RST_PIN",          "MUX_RST_PIN",    None),

    # ── PCA9685 PWM Driver ──
    ("PCA9685 PWM Driver", "PCA9685_ADDR",    "PCA9685_ADDR",    "hex_str"),
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    ("PCA9685 — Motor Channels", "MOTOR_LEFT_PWM_CHANNEL",  "PCA_CH_MOTOR_L_PWM", None),

    # ── Motor Control ──
    ("Motor Control", "MOTOR_STBY_PIN", "MOTOR_STBY_PIN", None),

    # ── MCP23017 GPIO Expander ──
    ("MCP23017 GPIO Expander", "MCP23017_ADDR", "MCP23017_ADDR", "hex_str"),
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    ("RCWL-1601 Rangefinders", "RCWL1601_I2C_ADDR", "RANGER_ADDR", "hex_str"),

    # ── Piezo Buzzer ──
    ("Piezo Buzzer", "PIEZO_PIN", "PIEZO_PIN", None),

    # ── UART0 header pads (nothing wired; the console is USB-Serial-JTAG) ──
    ("UART0 header pads", "UART0_TX_PIN", "UART0_TX_PIN", None),

    # ── Power latch and pack divider (socketed carrier, ADR-038) ──
    ("Power latch and pack monitor", "POWER_HOLD_PIN", "POWER_HOLD_PIN", None),
    ("Power latch and pack monitor", "PACK_SENSE_PIN", "PACK_SENSE_PIN", None),

    # ── MAX98357A I2S Audio ──
    ("MAX98357A I2S Audio", "I2S_BCLK_PIN",         "I2S_BCLK_PIN", None),
    ("MAX98357A I2S Audio", "I2S_LRCLK_PIN",        "I2S_LRCLK_PIN", None),
    ("MAX98357A I2S Audio", "I2S_DIN_PIN",          "I2S_DIN_PIN", None),
    ("MAX98357A I2S Audio", "AUDIO_SAMPLE_RATE_HZ", "AUDIO_SAMPLE_RATE_HZ", None),

    # ── Planner cadence (planner_task.h, plan_activity.h) ──
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
BALANCEBOT_EXTRACT = [
    # ── MPU6050 IMU (I2C1) ──
    ("MPU6050 IMU (I2C1)", "PIN_IMU_SDA", "PIN_IMU_SDA", None),
    ("MPU6050 IMU (I2C1)", "PIN_IMU_SCL", "PIN_IMU_SCL", None),
    ("MPU6050 IMU (I2C1)", "PIN_IMU_INT", "PIN_IMU_INT", None),

    # ── DRV8825 Stepper Drivers ──
    ("DRV8825 Stepper Drivers", "PIN_STEP_LEFT",     "PIN_STEP_LEFT",     None),
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
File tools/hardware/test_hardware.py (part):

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        with tempfile.TemporaryDirectory() as tmp:
            h = write(
                Path(tmp) / "a.h",
                "#define A_H\n#define I2C_SDA_PIN GPIO_NUM_5\n",
            )
            self.assertEqual(parse_defines([h]), {"I2C_SDA_PIN": "GPIO_NUM_5"})

    def test_conflicting_redefinition_is_an_error(self):
        # Output would otherwise depend on argument order.
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class RobocarConventionTest(unittest.TestCase):
    def test_only_gpio_num_macros_are_roles(self):
        defines = {
            "I2C_SDA_PIN": "GPIO_NUM_5",
            "I2C_MASTER_FREQ_HZ": "400000",
            "PCA9685_ADDR": "0x40",
            "MOTOR_LEFT_PWM_CHANNEL": "13",
        }
        self.assertEqual(roles_from_defines(defines, "robocar"), {"I2C_SDA_PIN": 5})

    def test_unknown_convention_is_an_error_naming_the_known_ones(self):
        with self.assertRaisesRegex(HardwareError, "balancebot.*robocar"):
            roles_from_defines({}, "gamepad-synth")

    def test_a_bare_integer_is_not_a_robocar_pin_even_with_a_pin_name(self):
        self.assertEqual(roles_from_defines({"PIN_IMU_SDA": "6"}, "robocar"), {})


class BalancebotConventionTest(unittest.TestCase):
    def test_pin_prefixed_bare_integers_are_roles(self):
        defines = {
            "PIN_IMU_SDA": "6",
            "PIN_STATUS_LED": "25",
            "CONTROL_LOOP_HZ": "500",  # a bare integer, but not a pin
            "MPU6050_ADDR": "0x68",
            "SPIN_COUNT": "3",  # PIN_ inside the name, not at its start
            "PIN_ALIAS": "PIN_IMU_SDA",  # not an integer
        }
        self.assertEqual(
            roles_from_defines(defines, "balancebot"),
            {"PIN_IMU_SDA": 6, "PIN_STATUS_LED": 25},
        )

    def test_gpio_num_values_are_not_balancebot_pins(self):
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        self.assertEqual(
            roles_from_defines(defines, "balancebot"),
            {
                "PIN_IMU_SDA": 6,
                "PIN_IMU_SCL": 7,
                "PIN_IMU_INT": 5,
                "PIN_STEP_LEFT": 2,
                "PIN_STEP_RIGHT": 3,
                "PIN_DIR_LEFT": 4,
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                "PIN_BATT_ADC_ENABLE": 19,
                "PIN_RGB_DATA": 22,
                "PIN_RGB_POWER": 23,
                "PIN_PACK_SENSE": 26,
                "PIN_EXP_D1": 27,
                "PIN_EXP_D2": 28,
            },
        )

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        # #722: a pin conflict is a wiring error, so the join reports it
        # rather than leaving it to surface as a router failure. The second
        # role is excused, so the conflict alone can be what fails.
        header = HEADER_H + "#define PIEZO_PIN GPIO_NUM_1\n"
        sidecar = SIDECAR + '\n[[undrawn]]\nrole = "PIEZO_PIN"\nwhy = "test"\n'
        with self.assertRaises(HardwareError) as ctx:
            self.join(self.make(sidecar=sidecar, header=header))
        message = str(ctx.exception)
        self.assertIn("LED_PIN", message)
        self.assertIn("PIEZO_PIN", message)
        self.assertIn("GPIO1", message)

    def test_a_macro_naming_another_role_is_an_alias_not_a_second_role(self):
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
    def test_a_rail_on_a_channel_net_fails(self):
        rail = '\n[[rails]]\nname = "5V"\nfrom = "mcu.5V"\nto = ["{}"]\n'
        for pin, role in (("motor.PWMA", "SPEED_CHANNEL"), ("drv.1", "SPEED_CHANNEL")):
            with (
                self.subTest(pin=pin),
                self.assertRaisesRegex(HardwareError, f"{pin}.*{role}"),
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
    def test_dropping_an_undrawn_entry_from_the_committed_sidecar_fails(self):
        # The completeness gate (#460) holds on the real project, not only on
        # the synthetic one: in the harness view UART0_TX_PIN is excused only by
        # this entry (the carrier wires it to the UART0 tap).
        text = (ROBOCAR / "hardware.toml").read_text(encoding="utf-8")
        entry = re.search(
            r'\[\[undrawn\]\]\nrole = "UART0_TX_PIN"\nbuild = "harness"\n'
            r'why = "[^"\n]*"\n\n?',
            text,
        )
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            (proj / "hardware.toml").write_text(
                text.replace(entry.group(0), ""), encoding="utf-8"
            )
            with self.assertRaisesRegex(HardwareError, "UART0_TX_PIN"):
                join(proj, repo_root=REPO_ROOT)

    def test_moving_the_piezo_onto_the_mux_reset_fails(self):
        # #722's repro: PIEZO_PIN GPIO_NUM_2 -> GPIO_NUM_3, which is now
        # TCA9548A_RST_PIN's pin (#782; it was the ultrasonic trigger's). Every
        # generator used to accept it; the router failed later.
        header = (ROBOCAR / "main/pin_config.h").read_text(encoding="utf-8")
        moved = header.replace(
            "#define PIEZO_PIN GPIO_NUM_2", "#define PIEZO_PIN GPIO_NUM_3"
        )
        self.assertNotEqual(moved, header)
        with tempfile.TemporaryDirectory() as tmp:
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            with self.assertRaises(HardwareError) as ctx:
                join(proj, repo_root=REPO_ROOT)
        message = str(ctx.exception)
        self.assertIn("PIEZO_PIN", message)
        self.assertIn("TCA9548A_RST_PIN", message)
        self.assertIn("GPIO3", message)

    def test_i2s_lands_on_the_amp_via_d8_d9_d10(self):
        nets = {n.role: (n.part, n.pin) for n in self.model.nets}
        self.assertEqual(nets["I2S_BCLK_PIN"], ("amp", "BCLK"))
        self.assertEqual(self.model.pin_for("I2S_BCLK_PIN").name, "D8")
        self.assertEqual(self.model.pin_for("I2S_LRCLK_PIN").name, "D9")
        self.assertEqual(self.model.pin_for("I2S_DIN_PIN").name, "D10")

    def test_the_microphone_is_excused_and_on_no_header_pad(self):
        undrawn = {u.role for u in self.model.undrawn}
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        # and WIRING.md stop hand-typing GPIO43. D7 is no longer UART0 RX here:
        # it is the power latch's HOLD output (ADR-038, #1270).
        undrawn = {u.role for u in self.model.undrawn}
        self.assertIn("UART0_TX_PIN", undrawn)
        self.assertEqual(self.model.pin_for("UART0_TX_PIN").name, "D6")

    def test_the_power_latch_and_pack_divider_pads_are_d7_and_d3(self):
        # The harness has no switch or divider, so both are excused there; the
        # carrier wires them.
        undrawn = {u.role for u in self.model.undrawn}
        self.assertLessEqual({"POWER_HOLD_PIN", "PACK_SENSE_PIN"}, undrawn)
        self.assertEqual(self.model.pin_for("POWER_HOLD_PIN").name, "D7")
        self.assertEqual(self.model.pin_for("PACK_SENSE_PIN").name, "D3")

    def rail_of(self) -> dict[tuple[str, str], str]:
        return {(e.part, e.pin): r.name for r in self.model.rails for e in r.loads}
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
    def test_the_motor_driver_mapping_agrees_with_pin_config_comments(self):
        # pin_config.h states the PCA9685 -> TB6612FNG mapping in comments
        # (`// -> PWMA`); hardware.toml states it as nets. Pin the two together.
        text = (ROBOCAR / "main/pin_config.h").read_text(encoding="utf-8")
        claimed = dict(re.findall(r"#define (\w+_CHANNEL) \d+\s*// -> (\w+)", text))
        joined = {
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            )
            (proj / "hardware.toml").write_text(sidecar)
            text = self.run_generator(REPO_ROOT, str(proj)).decode()
        self.assertIn("#let PIN_IMU_SDA = 6\n", text)
        self.assertIn("#let PIN_MOTOR_NENABLE = 1\n", text)
        self.assertIn("#let PIN_BATT_ADC_ENABLE = 19\n", text)
        self.assertNotIn("I2C_SDA_PIN", text)
        # Not mounted in the root justfile, so it names the script itself.
        self.assertIn(
            "regenerate with `python3 tools/typst/generate-pin-defs.py ", text
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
